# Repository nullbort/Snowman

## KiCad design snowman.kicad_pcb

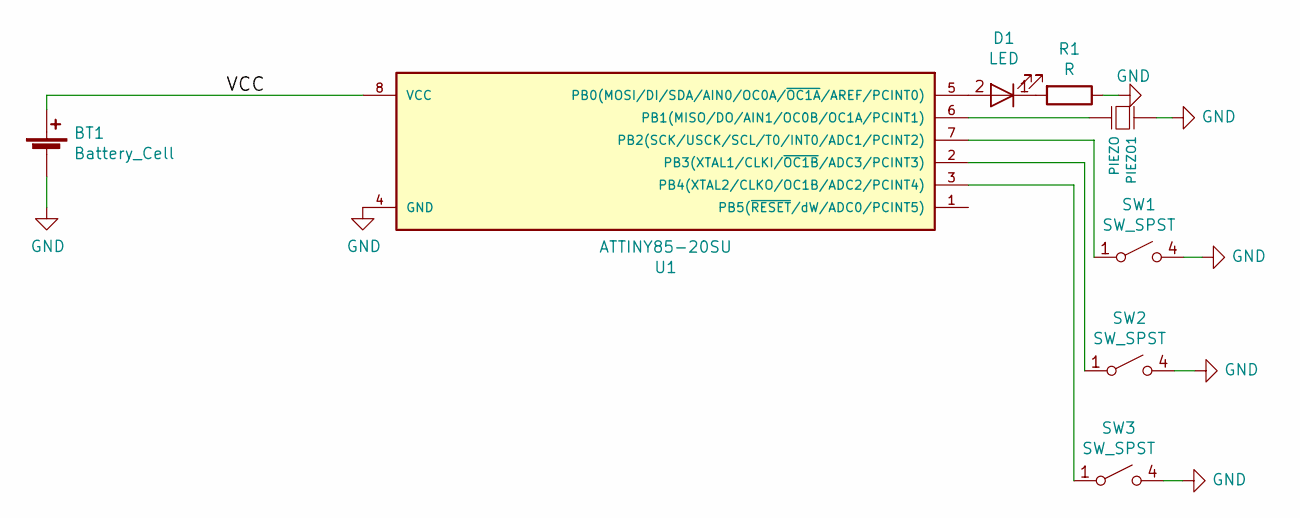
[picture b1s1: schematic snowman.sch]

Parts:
BT1: Battery_Cell; Keystone_3002_1x2032-CoinCell; DigiKey 36-3002CT-ND
D1: LED; LED_D3.0mm; DigiKey 846-1190-ND
PIEZO1: PIEZO; Piezo-PKMCS0909E4000-R1; DigiKey 490-4683-1-ND
R1: R; R_0603_HandSoldering; DigiKey 311-100HRCT-ND
SW1, SW2, SW3: SW_SPST; Button_SMD-PTS525SM15SMTR2-LFS; DigiKey CKN9104CT-ND
U1: ATTINY85-20SU; ATTiny85-20SU; DigiKey ATTINY85-20SU-ND

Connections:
/VCC: BT1.1 (+), U1.8 (VCC)
GND: BT1.2 (-), PIEZO1.1, R1.1, SW1.4 (B), SW2.4 (B), SW3.4 (B), U1.4 (GND)
unnamed: D1.1 (K), R1.2
unnamed: D1.2 (A), U1.5 (PB0(MOSI/DI/SDA/AIN0/OC0A/~OC1A~/AREF/P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)
unnamed: PIEZO1.2, U1.6 (PB1(MISO/DO/AIN1/OC0B/OC1A/PCINT1))
unnamed: SW1.1 (A), U1.7 (PB2(SCK/USCK/SCL/T0/INT0/ADC1/PCINT2))
unnamed: SW2.1 (A), U1.2 (PB3(XTAL1/CLKI/~OC1B~/ADC3/PCINT3))
unnamed: SW3.1 (A), U1.3 (PB4(XTAL2/CLKO/OC1B/ADC2/PCINT4))

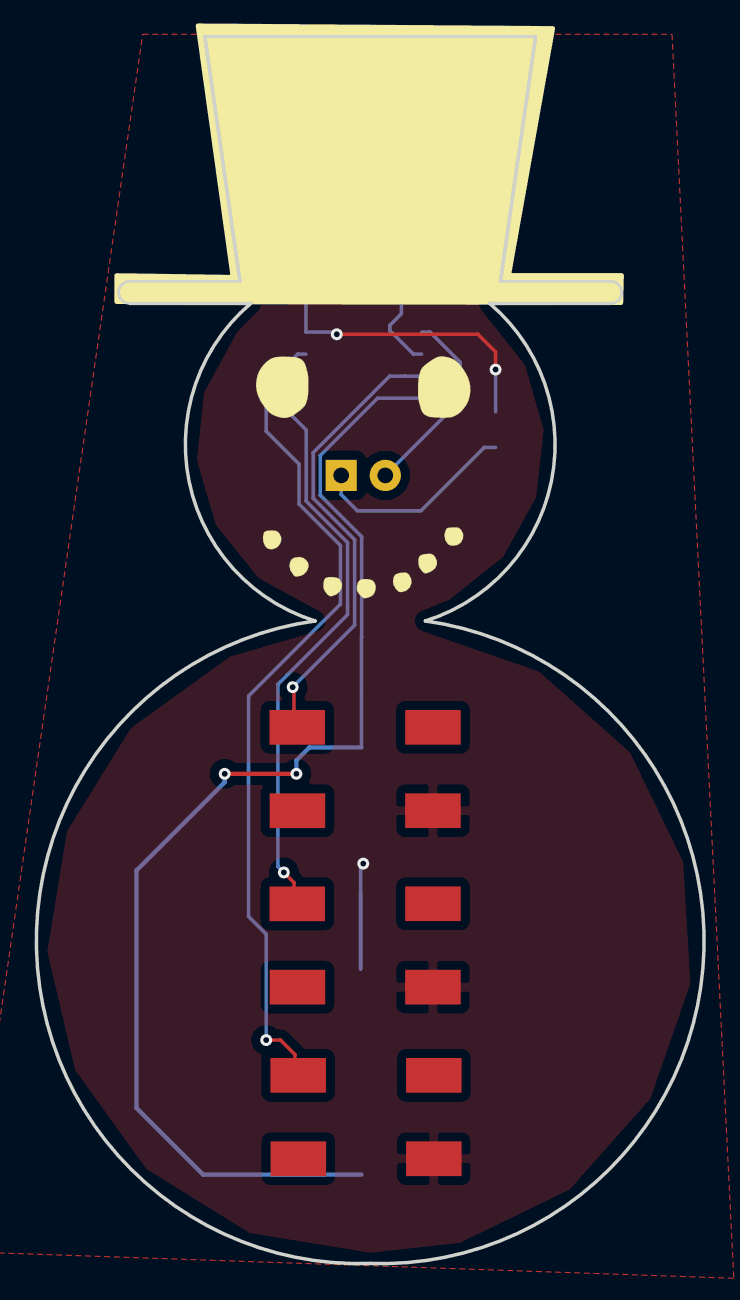
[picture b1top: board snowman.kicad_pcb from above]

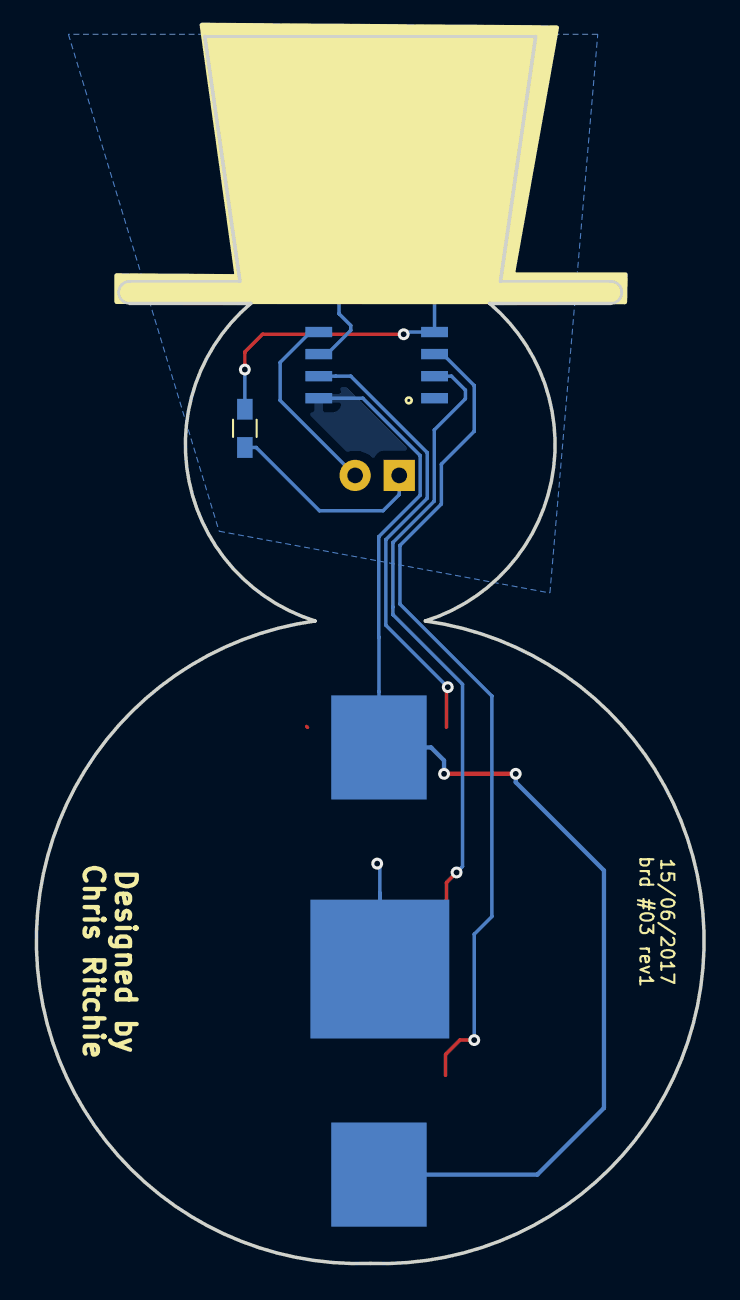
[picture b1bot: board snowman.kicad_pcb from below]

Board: 2 copper layers, 38.4 x 70.7 mm, 8 parts (3 on the bottom side), 8 nets.

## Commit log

2017-06-17 Stage files
2017-06-17 Added files
2017-06-17 Updated notes.txt
2017-07-07 Update ATTiny Footprint
    Add circle beside pad 1 of ATTiny
2017-07-08 Update Footprints
    Update piezo buzzer footprint, making it wider for easier hand soldering.
    Update button schematic to change pin 2 to pin 4 to match buttons being used
    Update LED footprint in schematic to 3mm
2017-07-08 Update Silkscreen
    Add rev1 to date and board number silkscreen
2017-07-15 Add DigiKey Product ID
    Add DigiKey product id's to all parts for creating BOM file
    Add price spreadsheet
2017-07-15 Remove Silk Screen From LED
    Create new footprint for 3mm LED without silk screen
2017-09-06 Shink VCC Copper Zone
    Shrink VCC copper zone on back of board so any possible scratches on PCB won't make contact with negative side of battery
2017-11-12 KiCad Symbol Update
    Update to how KiCad uses symbols
